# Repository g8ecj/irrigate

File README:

This is the irrigation controller.

It uses a number of DS2413 1-wire dual channel GPIO chips to drive triacs to operate
valves and pumps. It also optionally monitors 2 temperature sensors to implement 
a preset frost protection program and monitors the current drawn by the valves to 
ensure they are connected correctly.

The 1-wire bus with these devices on it is driven from a DS2480B UART to 1-wire Master 
Controller chip which is connected to one of the serial ports available on a modified
Linksys WRT54GL wireless router. It has also been used with a TPLINK WR1043ND router
and a USB9097 USB 1-wire master dongle.

The router has Open Source software available for it that not only frees the 
user from the limits of the manufacturers code but also provides the cross compile 
environment to allow addition functions to be added by anyone.
See http://openwrt.org

It uses the owfs system that makes 1-wire devices appear as a part of the file system.
The interface to the owlib software is via the owcapi 'C' API library.

These files implement an embedded http server with simple callbacks to the main code. It
is licensed under the MIT License which basically says do what you like so long as the 
license conditions remain in the files! I'm using version 5.2 at present.

   mongoose.c
   mongoose.h

These files are totally new and provide all of the AJAX web interface, the onewire interface,
statistics, time event queueing, scheduling, command line parsing and error handling.
They are released under the GNU Public License version 2.

   irr_actions.c
   irr_chanmap.c
   irr_onewire.c
   irr_parse.c
   irr_queue.c
   irr_schedule.c
   irr_stats.c
   irr_utils.c
   irr_web.c
   irrigate.c

External libraries to parse and generate JavaScript Object Notation (JSON) data for the AJAX 
methods used in the web interface. The javascript widgets for timeline support are from 
the CHAPS links library and are available under the Apache license. Other javascript code has
been released to the public domain.

The makefile will do a native build under Linux by defining a 'PC' target that causes a 1-wire simulator
to be built.

Compiling under OpenWrt simple. Unpack the compressed file 'openwrt-package' that provides the 
package makefile and control files for native packaging and installation into the 'package'
directory. Configure the system to build the package by running 'make menuconfig' and select
    'Utils' -> 'irrigate'
            -> 'Filesystem' -> 'owfs'
    'Libraries' -> 'libjson'
                -> 'Filesystems' -> 'libow'
                                 -> 'libow-capi'
These can all be built as modules or built into the main image.

Kernel modules to consider depend on the 1-wire interface in use. The USB9097 requires the 
'kmod-usb-serial-ch341' module USB/UART driver for example.

Save the new config and then build the whole system using 'make'. Install to the target as a
complete image or using 'opkg' package manager if using modules.

$ ./irrigate --help
irrigate: Irrigation Controller Version 2.00 Copyright (c) 2009-2011 Robin Gilks
usage: ./irrigate [bcdfhlprstvx]

-a <file>, --file      access log file name
-b,        --background run in daemon mode
-c,        --config    configure zone mapping
-d <dir>,  --datapath  data file directory
-f <file>, --file      config file name
-l <int>,  --limit     degree-minutes before frost program runs
-m,        --monitor   check current drawn by solenoid valves
-p <int>,  --port      http port number
-r <dir>,  --root      http root directory
-s <dev>,  --serialport serial port device
-t <int>,  --threshold temperature below which frost protect operates
-v,        --version   useful version information
-x <int>   --debug     debug mode
-h,        --help      this help screen

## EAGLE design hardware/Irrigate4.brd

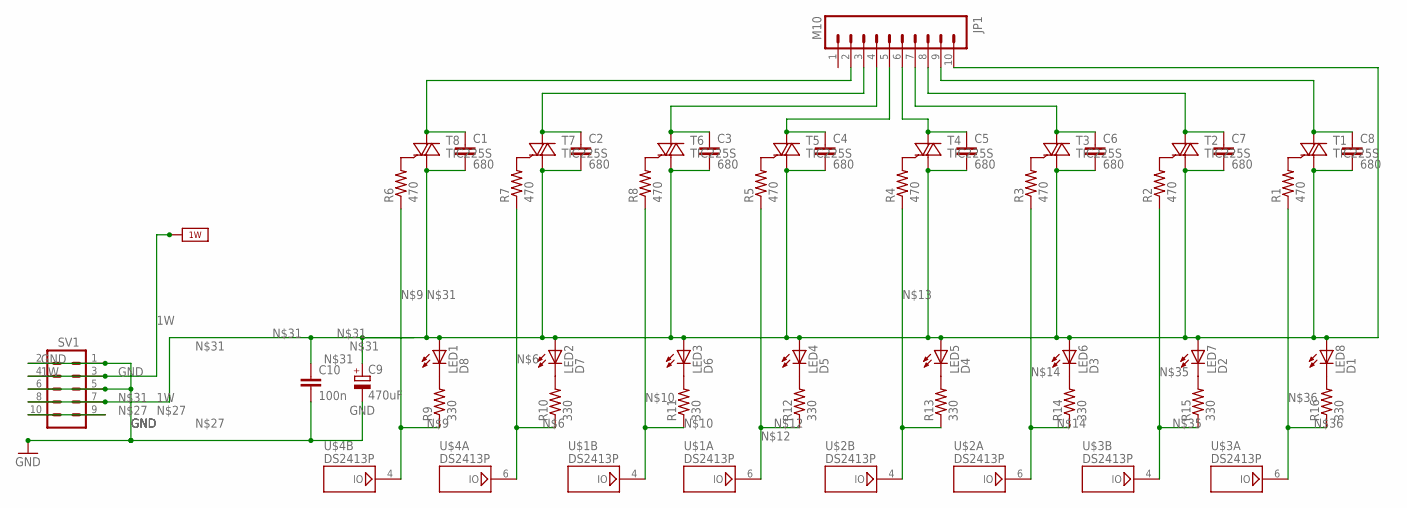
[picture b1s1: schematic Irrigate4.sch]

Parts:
C1, C2, C3, C4, C5, C6, C7, C8: 680; C050-045X075
C9: 470uF; E5-8,5
C10: 100n; C050-024X044
JP1: M10; 10X10MM
LED1: D8; LED3MM
LED2: D7; LED3MM
LED3: D6; LED3MM
LED4: D5; LED3MM
LED5: D4; LED3MM
LED6: D3; LED3MM
LED7: D2; LED3MM
LED8: D1; LED3MM
R1, R2, R3, R4, R5, R6, R7, R8: 470; AXIAL-0.3
R9, R10, R11, R12, R13, R14, R15, R16: 330; AXIAL-0.3
SV1: M05X2PTH; AVR_ICSP
T1, T2, T3, T4, T5, T6, T7, T8: TIC225S; TO220DS
U$1, U$2, U$3, U$4: DS2413P; TSOC6

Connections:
1W: SV1.3, SV1.4, U$1.2 (1W), U$2.2 (1W), U$3.2 (1W), U$4.2 (1W)
GND: C9.-, C10.2, SV1.1, SV1.2, SV1.5, SV1.6, U$1.1 (GND), U$1.5 (GND), U$2.1 (GND), U$2.5 (GND), U$3.1 (GND), U$3.5 (GND), U$4.1 (GND), U$4.5 (GND)
unnamed: R1.P$2 (2), T1.G
unnamed: R2.P$2 (2), T2.G
unnamed: R3.P$2 (2), T3.G
unnamed: R4.P$2 (2), T4.G
unnamed: R5.P$2 (2), T5.G
unnamed: R7.P$1 (1), R10.P$1 (1), U$4.6 (IO)
unnamed: R7.P$2 (2), T7.G
unnamed: R6.P$2 (2), T8.G
unnamed: R6.P$1 (1), R9.P$1 (1), U$4.4 (IO)
unnamed: R8.P$1 (1), R11.P$1 (1), U$1.4 (IO)
unnamed: R8.P$2 (2), T6.G
unnamed: R5.P$1 (1), R12.P$1 (1), U$1.6 (IO)
unnamed: R4.P$1 (1), R13.P$1 (1), U$2.4 (IO)
unnamed: R3.P$1 (1), R14.P$1 (1), U$2.6 (IO)
unnamed: LED5.K (C), R13.P$2 (2)
unnamed: LED6.K (C), R14.P$2 (2)
unnamed: LED7.K (C), R15.P$2 (2)
unnamed: C8.1, JP1.9, T1.A2
unnamed: C7.1, JP1.8, T2.A2
unnamed: C6.1, JP1.7, T3.A2
unnamed: C5.1, JP1.6, T4.A2
unnamed: C4.1, JP1.5, T5.A2
unnamed: C3.1, JP1.4, T6.A2
unnamed: C2.1, JP1.3, T7.A2
unnamed: C1.1, JP1.2, T8.A2
unnamed: LED8.K (C), R16.P$2 (2)
unnamed: SV1.9, SV1.10
unnamed: LED1.K (C), R9.P$2 (2)
unnamed: LED2.K (C), R10.P$2 (2)
unnamed: C1.2, C2.2, C3.2, C4.2, C5.2, C6.2, C7.2, C8.2, C9.+, C10.1, JP1.10, LED1.A, LED2.A, LED3.A, LED4.A, LED5.A, LED6.A, LED7.A, LED8.A, SV1.7, SV1.8, T1.A1, T2.A1, T3.A1, T4.A1, T5.A1, T6.A1, T7.A1, T8.A1
unnamed: LED3.K (C), R11.P$2 (2)
unnamed: LED4.K (C), R12.P$2 (2)
unnamed: R2.P$1 (1), R15.P$1 (1), U$3.4 (IO)
unnamed: R1.P$1 (1), R16.P$1 (1), U$3.6 (IO)

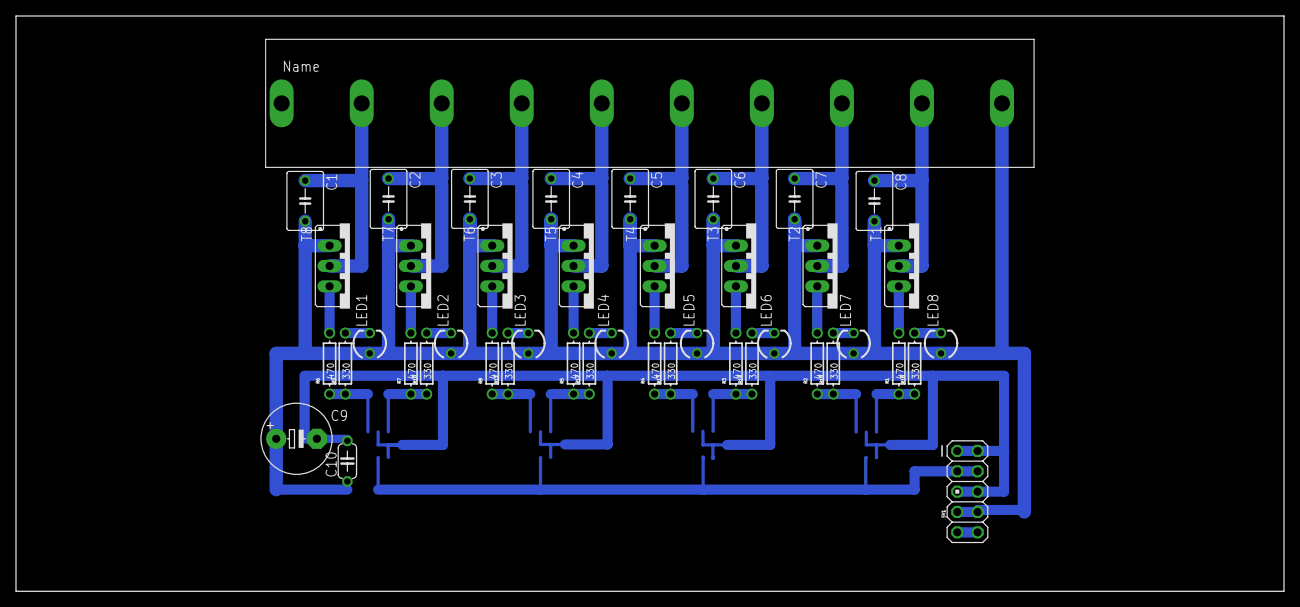
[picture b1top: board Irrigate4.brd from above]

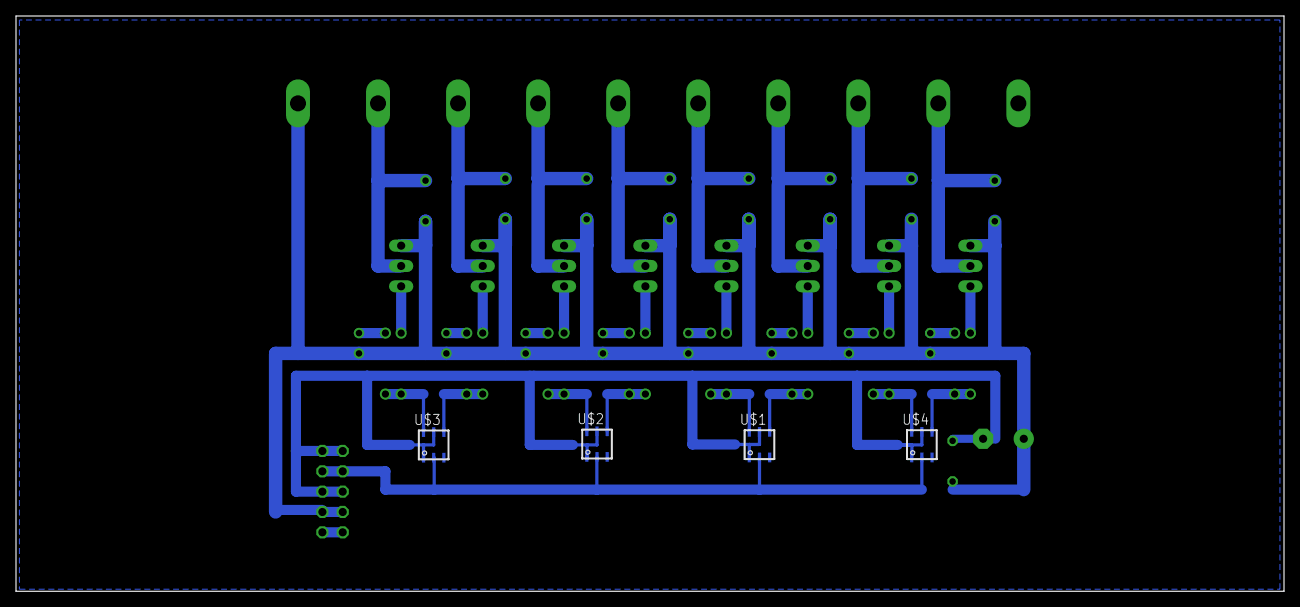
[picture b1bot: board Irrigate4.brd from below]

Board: 2 copper layers, 158.4 x 71.9 mm, 48 parts (4 on the bottom side), 36 nets.

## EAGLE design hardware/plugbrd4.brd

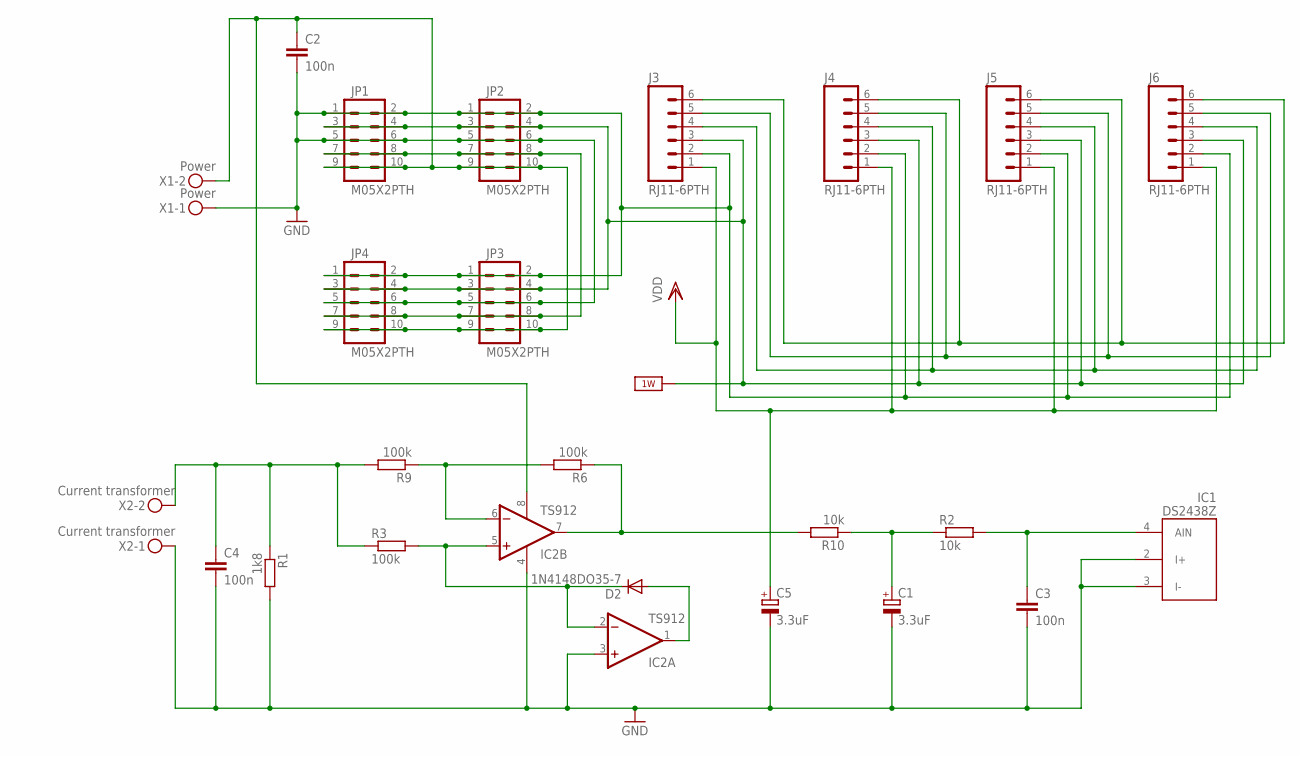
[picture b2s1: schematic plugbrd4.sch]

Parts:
C1, C5: 3.3uF; E5-6
C2, C3, C4: 100n; C050-025X075
D2: 1N4148DO35-7; DO35-7
IC1: DS2438Z; SO08
IC2: TS912; SO08
J3, J4, J5, J6: RJ11-6PTH; RJ11-6
JP1, JP2, JP3, JP4: M05X2PTH; AVR_ICSP
R1: 1k8; 0207/12
R2, R10: 10k; 0207/12
R3, R6, R9: 100k; 0207/12
X1: Power; MKDSN1,5/2-5,08
X2: Current transformer; MKDSN1,5/2-5,08

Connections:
1W: IC1.8 (1W), J3.3, J4.3, J5.3, J6.3, JP1.3, JP1.4, JP2.3, JP2.4, JP3.3, JP3.4, JP4.3, JP4.4
GND: C1.-, C2.2, C3.2, C4.2, C5.-, IC1.1 (GND), IC1.2 (I+), IC1.3 (I-), IC2.3 (+IN), IC2.4 (V-), J3.2, J4.2, J5.2, J6.2, JP1.1, JP1.2, JP1.5, JP1.6, JP2.1, JP2.2, JP2.5, JP2.6, JP3.1, JP3.2, JP3.5, JP3.6, JP4.1, JP4.2, JP4.5, JP4.6, R1.2, X1.1, X2.1
unnamed: C1.+, R2.1, R10.1
unnamed: JP1.7, JP1.8, JP2.7, JP2.8, JP3.7, JP3.8, JP4.7, JP4.8
unnamed: D2.A, IC2.1 (OUT)
unnamed: J3.4, J4.4, J5.4, J6.4
unnamed: J3.5, J4.5, J5.5, J6.5
unnamed: J3.6, J4.6, J5.6, J6.6
unnamed: IC2.7 (OUT), R6.1, R10.2
unnamed: IC2.6 (-IN), R6.2, R9.1
unnamed: C4.1, R1.1, R3.1, R9.2, X2.2
unnamed: C2.1, IC2.8 (V+), JP1.9, JP1.10, JP2.9, JP2.10, JP3.9, JP3.10, JP4.9, JP4.10, X1.2
unnamed: C3.1, IC1.4 (AIN), R2.2
unnamed: D2.C, IC2.2 (-IN), IC2.5 (+IN), R3.2
VDD: C5.+, IC1.5 (VDD), J3.1, J4.1, J5.1, J6.1

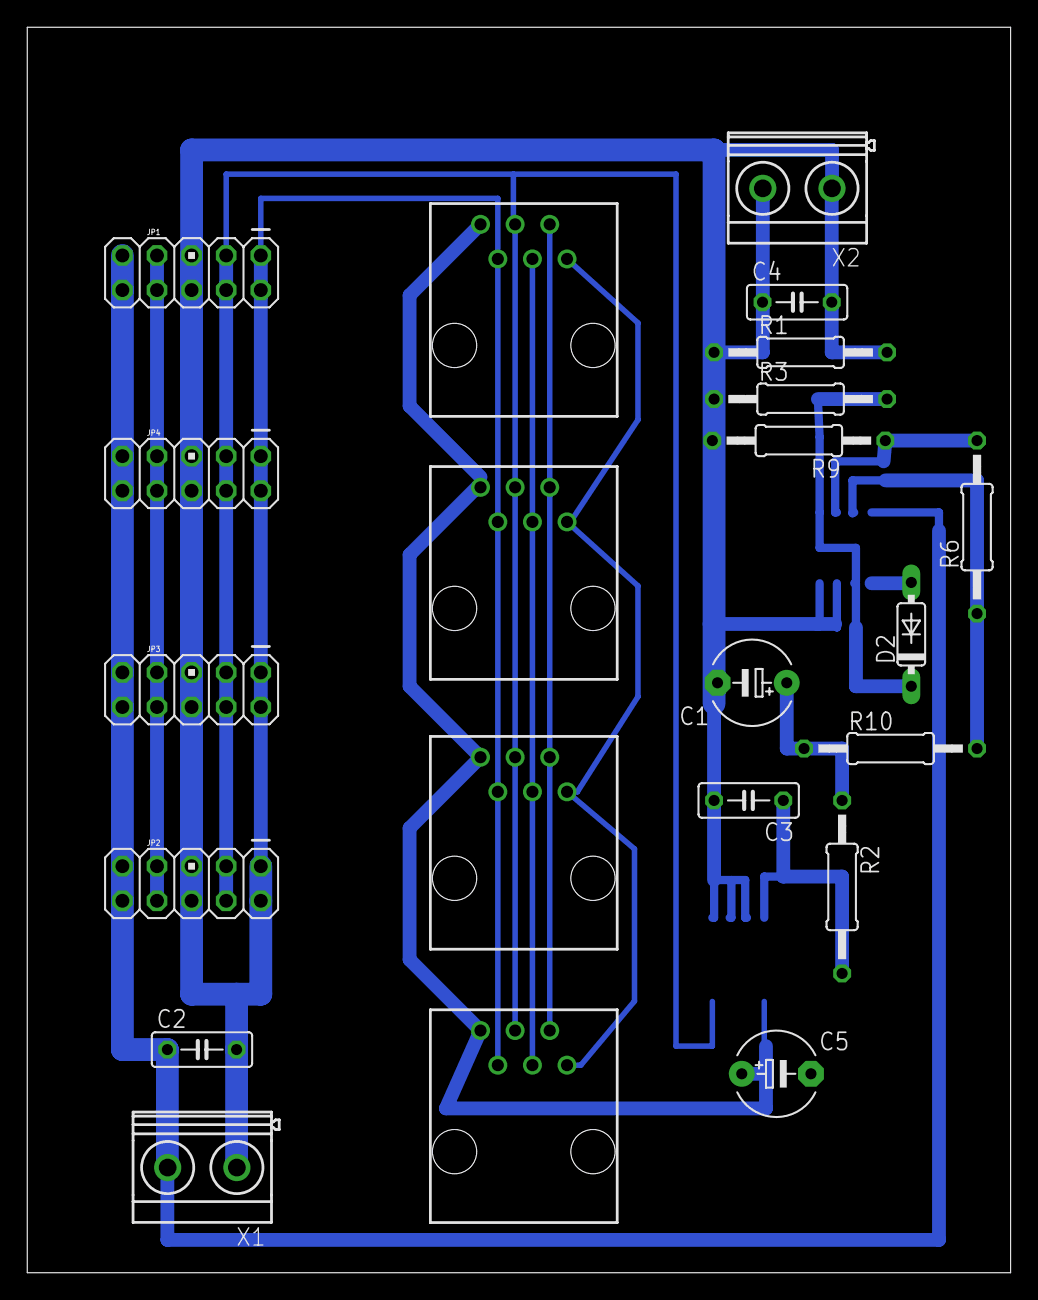
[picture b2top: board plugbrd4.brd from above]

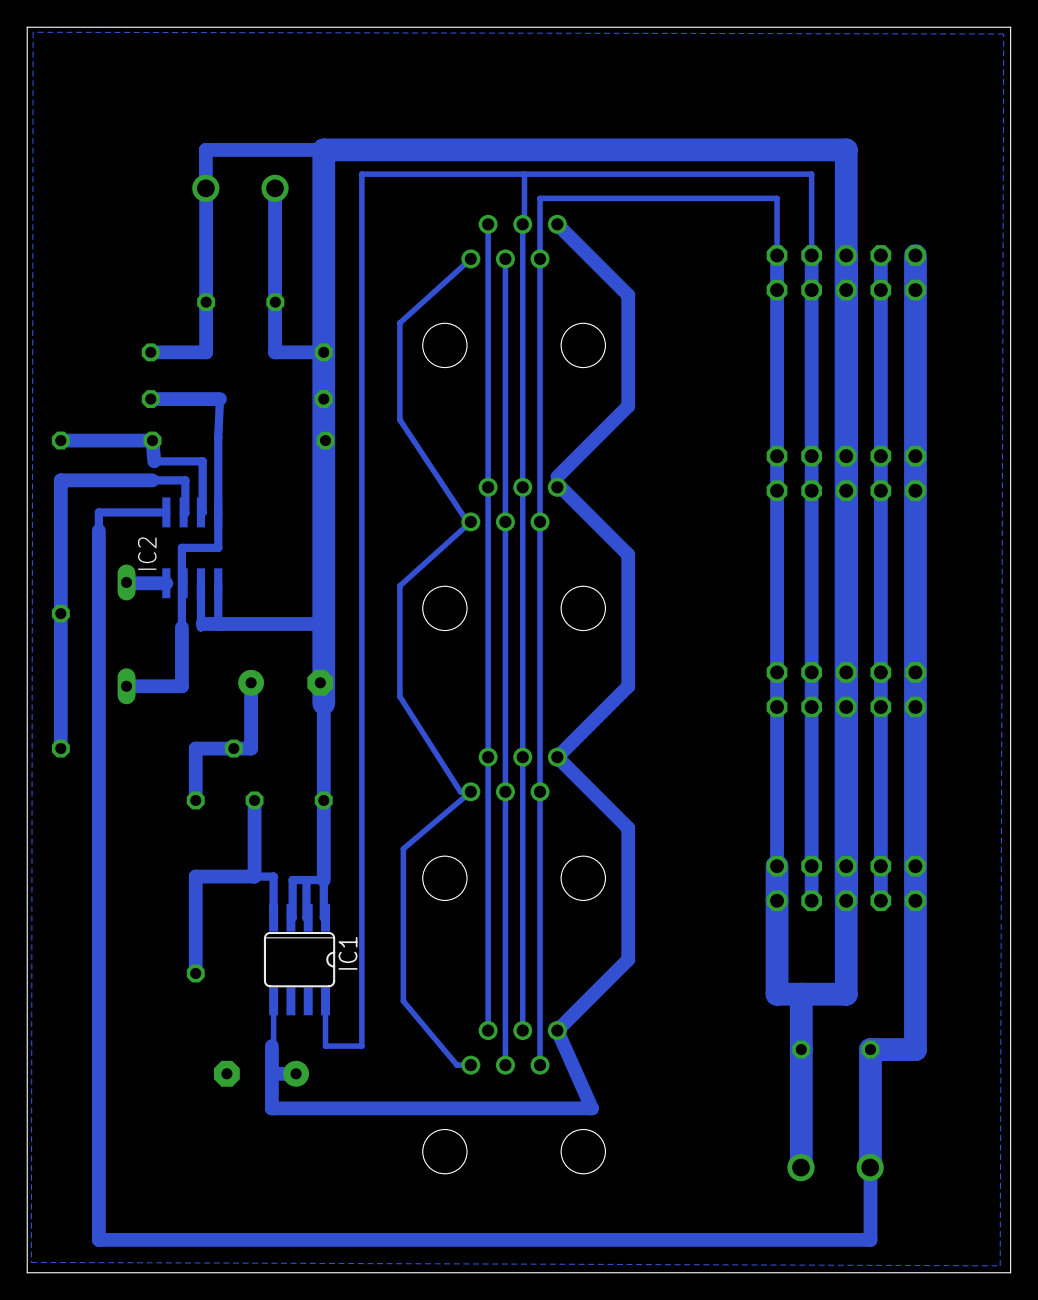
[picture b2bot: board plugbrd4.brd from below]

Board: 2 copper layers, 72.2 x 91.4 mm, 24 parts (2 on the bottom side), 15 nets.

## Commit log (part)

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2013-11-25 Created GIT repository based on version 2.3
2013-11-25 Updatd to latest Makefile for use in openwrt system
2013-12-25 Move calculation of total flow from being on-the-fly to polling all active zones Extract expected current poll to a function in the utils section
2013-12-25 Update current values for 22volt supply rather than old 25.5 volt (was blowing vavle solenoids)
2013-12-25 Correctly change current values - got it wrong!!
2013-12-27 Add an extra element to display the total flow on the main page
2013-12-27 Put favicon refs into html page.
2014-01-07 Move towards getting test mode working again!!
2014-01-07 Fix up problems with debug (PC) mode and test changes
2014-01-08 Ignore executable
2014-01-08 Convert all boolean to bool and remove typedef
2014-01-09 Update to mongoose 5.0 by putting back protect_uri functionality
2014-01-09 Remove web mutex, correct options so web server starts
2014-01-09 Revert protect_uri changes - ain't going to work!!
2014-01-09 Update version number and copyright years
2014-01-12 New authorise method
2014-01-12 Avoid name clash with timedata/timeline and use new mongoose API correctly for headers
2014-01-13 Update log commands to use mg_printf_data and send headers correctly
2014-01-13 Use duration from main testvalve virtual zone but adjust from minutes to seconds
2014-01-13 Fix up locking of domestic feed when in valve test mode
2014-01-13 New mongoose with send_auth exposed
2014-01-13 Remove all pthread references and mutexes
2014-01-14 Adjust debug dumps on usr signal
2014-01-15 Tidy up layout on main page
2014-01-16 Try and get well pump status during test mode to display correctly
2014-01-16 Prepend datafile path to passfile name
2014-01-16 Remove command line driven test mode - interactive one is more powerful now
2014-01-17 Handle durations in seconds throughout so very short periods can be used for test mode
2014-01-18 Fix memory leak in processing history file for timeline display
2014-01-22 Move derivation of mouseover title to server from browser
2014-02-12 New timeline from chap-links
2014-02-12 More work on new timeline js
2014-02-13 Implement repaint of program screen after exit from timeline
2014-02-14 Adjust colours of timeline items
2014-02-14 Ensure embedded target is stripped
2014-02-16 Create a nice sprinkly icon
2014-02-16 Make favicon references non-absolute
2014-02-16 Don't need the timeline images - not used by this app!!
2014-02-17 Remove no longer required json module (was used by Simile timeline), update documentation and help
2014-02-17 Extend timeline window to +/- 8 days, ensure day text is generated correctly
2014-02-17 Schedule up to 8 days ahead and keep 8 days of history
2014-02-18 Total rehash for owfs 1-wire interface
2014-02-18 Remove remaining public domain 1-wire interface headers etc
2014-02-19 More owfs changes
2014-02-19 Mostly done, may need a cleanup
2014-02-19 Clean compile stage, not debugged yet...
2014-02-19 Reset optind aftre parsing command line to prevent crash in ow_init()
2014-02-19 Make the best use of the owfs PIO handling. Fail if 1-wire port not available
2014-02-19 Update openwrt Makefile for lib dependencies
2014-02-20 Strip binary on compile and update README file.
2014-02-20 Speeling mistok
2014-02-20 Change back to cached I/O on gpio using PIO.BYTE path, make debug in owfs configurable
2014-02-20 Another rehash of the ds2413 pio manipulation!!
2014-02-20 Get sense of bits in general reset the right way up
2014-02-20 Exit if nothing found on 1-wire bus
2014-02-23 Minor debug changes, case insensitive compare on 1-wire addresses, extend RX timeout on serial interface
2014-02-23 Manual merge from owfs branch but continue with old Dallas PD s/w
2014-02-23 Unlock well pump if test mode cancelled, turn on valves in test mode
2014-02-23 Clean up locked mouseover and use proper unlock of well pump when test mode cancelled
2014-02-23 Correct version number and display locked status correctly
2014-02-23 Various bodges to try and fix owfs problems.
2014-02-23 Measure VAD from DS2438 through the uncached tree, clean up merge conflicts
2014-02-24 No need to set cache timeout to zero if using uncached tree, memory leak in get_temperature
2014-02-24 Forgot to update the ds2413 byte cache on successful write. Remove test data from spare12 zone
2014-02-26 More README - make openwrt options clearer
2014-02-27 Stray locked status from history items and correct OW_put call
2014-03-01 Highlight errors in timeline display using box, tidy main include
2014-03-02 May be a while before owfs endian bug gets fixed so make a fix here wrapped in a #define
2014-03-02 Rename to latest trendy suffix
2014-03-02 Try and format README with markdown code
2014-03-02 Opps - ignore passfile
2014-03-02 Opps
2014-03-02 Different keyboard, backticks in a differnt place...
2014-03-03 Start to define how to customise the display, build 1-wire sim by default on PC
2014-03-03 Put zoom capability back in, more documentation
2014-03-03 Provide an example password file of admin/admin and more documentations again!!
2014-03-03 Formatting...
2014-03-03 Update CUSTOMISATION.md
    speeling
2014-03-03 More documentation
2014-03-03 Describe -c switch to create basic config file
2014-03-09 Clean out global variables that are not really required, a few comments.
2014-03-10 Tidy up test mode and check for duplicate group in config
2014-03-10 Start a TODO list
2014-03-11 Missing bracket!!
2014-03-11 First cut at merging in new version 5.3 of mongoose
2014-03-11 Don't need to define memory target anymore
2014-03-11 Remove unwanted auth check calls, more debug
2014-03-11 We don't expect to use MG_POLL events, on the web server callback, so ignore them
2014-03-11 Update Copyright and license notices
2014-03-19 Work in progress for new pump handling
2014-03-19 Pump management still not quite right but mostly there now!!
2014-03-20 Looks like the pump algorithm is OK now. Uses new 'stock' flag to indicate a pump is used to supply stock water as well as irrigation
2014-03-20 The 'isstock' flag is only meaningful if there is no other demand
2014-03-20 Document the changes to pump handling that make it generic
2014-03-21 Add the password maintenance command line stuff and get and set time from one of the DS2438 chips
2014-03-22 Version number update to track new pump handling
2014-03-23 Read/write of time to ds2438 doesn't require uncached access
2014-03-24 Start to integrate DS18x20 temperature sensors into the scheme of things
2014-03-24 Fix syntax error in target (non-PC) build
2014-03-24 Make 1-wire family codes consistent
2014-03-27 Changes to pump handling to define a maximum run time for a pump
2014-03-27 Allow for more than 1 pump in the statistics recording
2014-03-27 Clean up stats handling, make more readable
2014-03-31 Note changes to statistics in the correct place!!
2014-03-31 Optimise pump stats
2014-04-02 Correct was_is decision in status description and reload status when switching from timeline screen
2014-04-03 Update temperature sensor index correctly
2014-04-03 Improve documentation
2014-04-04 Change default maxrun for stock water pump
2014-04-05 Better comments
2014-04-08 Start to make sensors configurable, make sure 'useful' flag changes don't affect display
2014-04-08 Up version number
2014-04-11 Start of config for sensors, read them in, diagnostic printout
2014-04-13 More updates for configurable sensors
2014-04-15 Major changes to differentiate between 1-wire devices from the configuration file rather than just looking at what type they are (which says nothing of what they are doing!) This has simplified lots 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
2014-04-15 Get some real 1-wire addresses for sensors into the default config
2014-04-15 Convert set/get time to use new sensor style config
2014-04-15 Markup bug
2014-04-15 Markup
2014-04-17 Tidy comments
2014-04-17 More docs
2014-04-21 make a cross reference from zone chanmap to the pump and sensor maps
2014-04-21 Up version
2014-05-02 Finish tidy up of program timeline screen switching
2014-05-24 If pump turn-on fails then wait locktime before retry. Update docs on new pump json keys
2014-06-16 Try and put a duration value into timeline active pump data
2014-06-17 Fine tune the timedata on active pumps
2014-06-17 More bugs in embedded compile
2014-07-01 Added uptime reporting, improved customisation docs, minor reformat
2014-07-01 Ensure an action that involves a 'cancel' queues the cancel right at the front of the action queue so it occurs first
2014-07-02 Optimise uptime code, don't report sensors in status data
2014-07-02 Make variable names more meaningful
2014-07-04 Tidy up error handling and report failure cause in history display
2014-07-05 Initialise strings to empty
2014-07-05 Up version number due to changing some of the status display logic (i.e. deleted some code!!)
2014-07-09 Improve time display of active pump mouseover
2014-08-11 Change lock time on failure to a fixed value rather than the (re)start time
2014-08-11 Don't display duplicate items (< failtime, unchanging error code)
2014-08-11 Extend failure lock time to 1 minute
2014-08-14 Update version, track zone for repeating history items
2014-08-20 All the basics for getting JSON data from the sensors to the AJAX browser frontend
2014-09-18 Statr to allow LCD attached via ds2408 on 1-wire bus.
2014-09-28 Split out sensor reading into its own callback, up version
2014-09-28 Remove RTC from sensor status, fix bugs!
2014-10-06 Change CSS back to the way it was, adjust frost threshold limits
2014-10-07 Generate all mouseover text for frost protect in server, not in html
2014-10-07 Up version number, capture new version of status info
2014-10-14 Bring across latest git version of mongoose
2014-11-02 Move chanmap init out of main; improve repeating starttime decode; improve statistics data dump; clean up irrelevant header stuff
2014-11-17 Make title string more useful
2014-11-18 Up version, tidy code!
2014-11-20 Implement 'last time run' for all zones in case I forget what went when!
2014-11-30 Protect password file, improve title display of currentlyactive zone(s)
2014-12-20 Calculate duration for statistics from the actual time run
2014-12-25 Split stats update to allow web interface to construct a human readable set of stat values as well as maintaining the statistics file. Make sure all relevant information is stored in the statistics f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
2014-12-25 Display factions of an hour correctly, up version number
2014-12-26 Put wiring info in the correct place
2014-12-26 Fix README
2014-12-26 Revert part of a previous commit that moved the clearing of starttime and frequency to the CANCEL action function rather than doing it directly in the function call.
2014-12-26 Convert all 'last duration' handling from minutes to seconds (the same as everything else!!)
2015-01-15 Tidy up the statistics gathering, make ready of json data transfer
2015-01-21 Major scheduling changes to allow repeating for multiple days of the week to be programmed as well as by interval. Up version.
2015-01-22 More major updates, this time to implement the display of statistics properly
2015-01-22 Make sure daylist really exists before parsing it
2015-01-22 Use the same methods for statistics display for the log display. Simplify display choice button.
2015-01-25 Put some comments into wiring file.
2015-02-02 Change format of json message used in logs
2015-02-07 Remove conditionals on json log data generation. Improve comments
2015-02-07 Make statistics page more readable by removing irrelevant data
2015-11-18 Change all depreciated instances of json_object_object_get() to json_object_object_get_ex(), allow ISFROST types in groups
2016-01-31 Don't clear zone details until we know which zone it is!!
2016-01-31 Allow delay and advance to be select choice of up to several days
2016-02-01 Up version to 4.5
2016-02-12 Change map class to unhide scrollbar on hover for dispaying log data
2016-03-10 Trap xmlhttprequest status != 200 as errors
2016-03-13 Tidy up ajax interface, remove extranious code, trigger timeout correctly, document functions
2016-05-17 Make sure that pumps stay locked until the general reset has completed.
2017-07-11 Try to use Chinese clones of ds2413
